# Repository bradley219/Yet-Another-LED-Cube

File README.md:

Yet-Another-LED-Cube
====================

About
-----
An attempt to reinvent..the cube? 

Sorry, this file hasn't had much effort put into it yet :/ A [video](https://fastl.io/eX6) to hold you over for now.

Schematic available in PDF and Eagle formats in the \`schematic' directory

Hardware
--------

### LED Matrix Topography

Since I only had enough hardware to create a 4x4x4 cube, I wanted the display to be as robust as
possible. I opted to use the [TLC5940](http://www.ti.com/product/tlc5940) 16-channel constant-current LED driver from Texas
Instruments, which provides 16 independent 12-bit PWM channels, each of which can sink &gt;100mA 
of current. My goal was to be able to use a single 16-channel driver to drive all 192 channels by
using a multiplexing scheme. To acheive this, I grouped the LEDs into individual "pages" of 4 LEDs.
The LEDs within a "page" share a common anode; cathodes are shared among LEDs in corresponding
positions within other pages.

### Drive Theory and Timing

The design of the cube allows for only a single "page" of LEDs to be driven at any given moment. The
16 pages which make up the cube are driven in sequence at about 100Hz (full-cycle period). 

### High-Side Switching
### Low-Side Switching/Current Sink

Software
--------

### Driver
### Driver Interface
### Color Calculations
### Animations

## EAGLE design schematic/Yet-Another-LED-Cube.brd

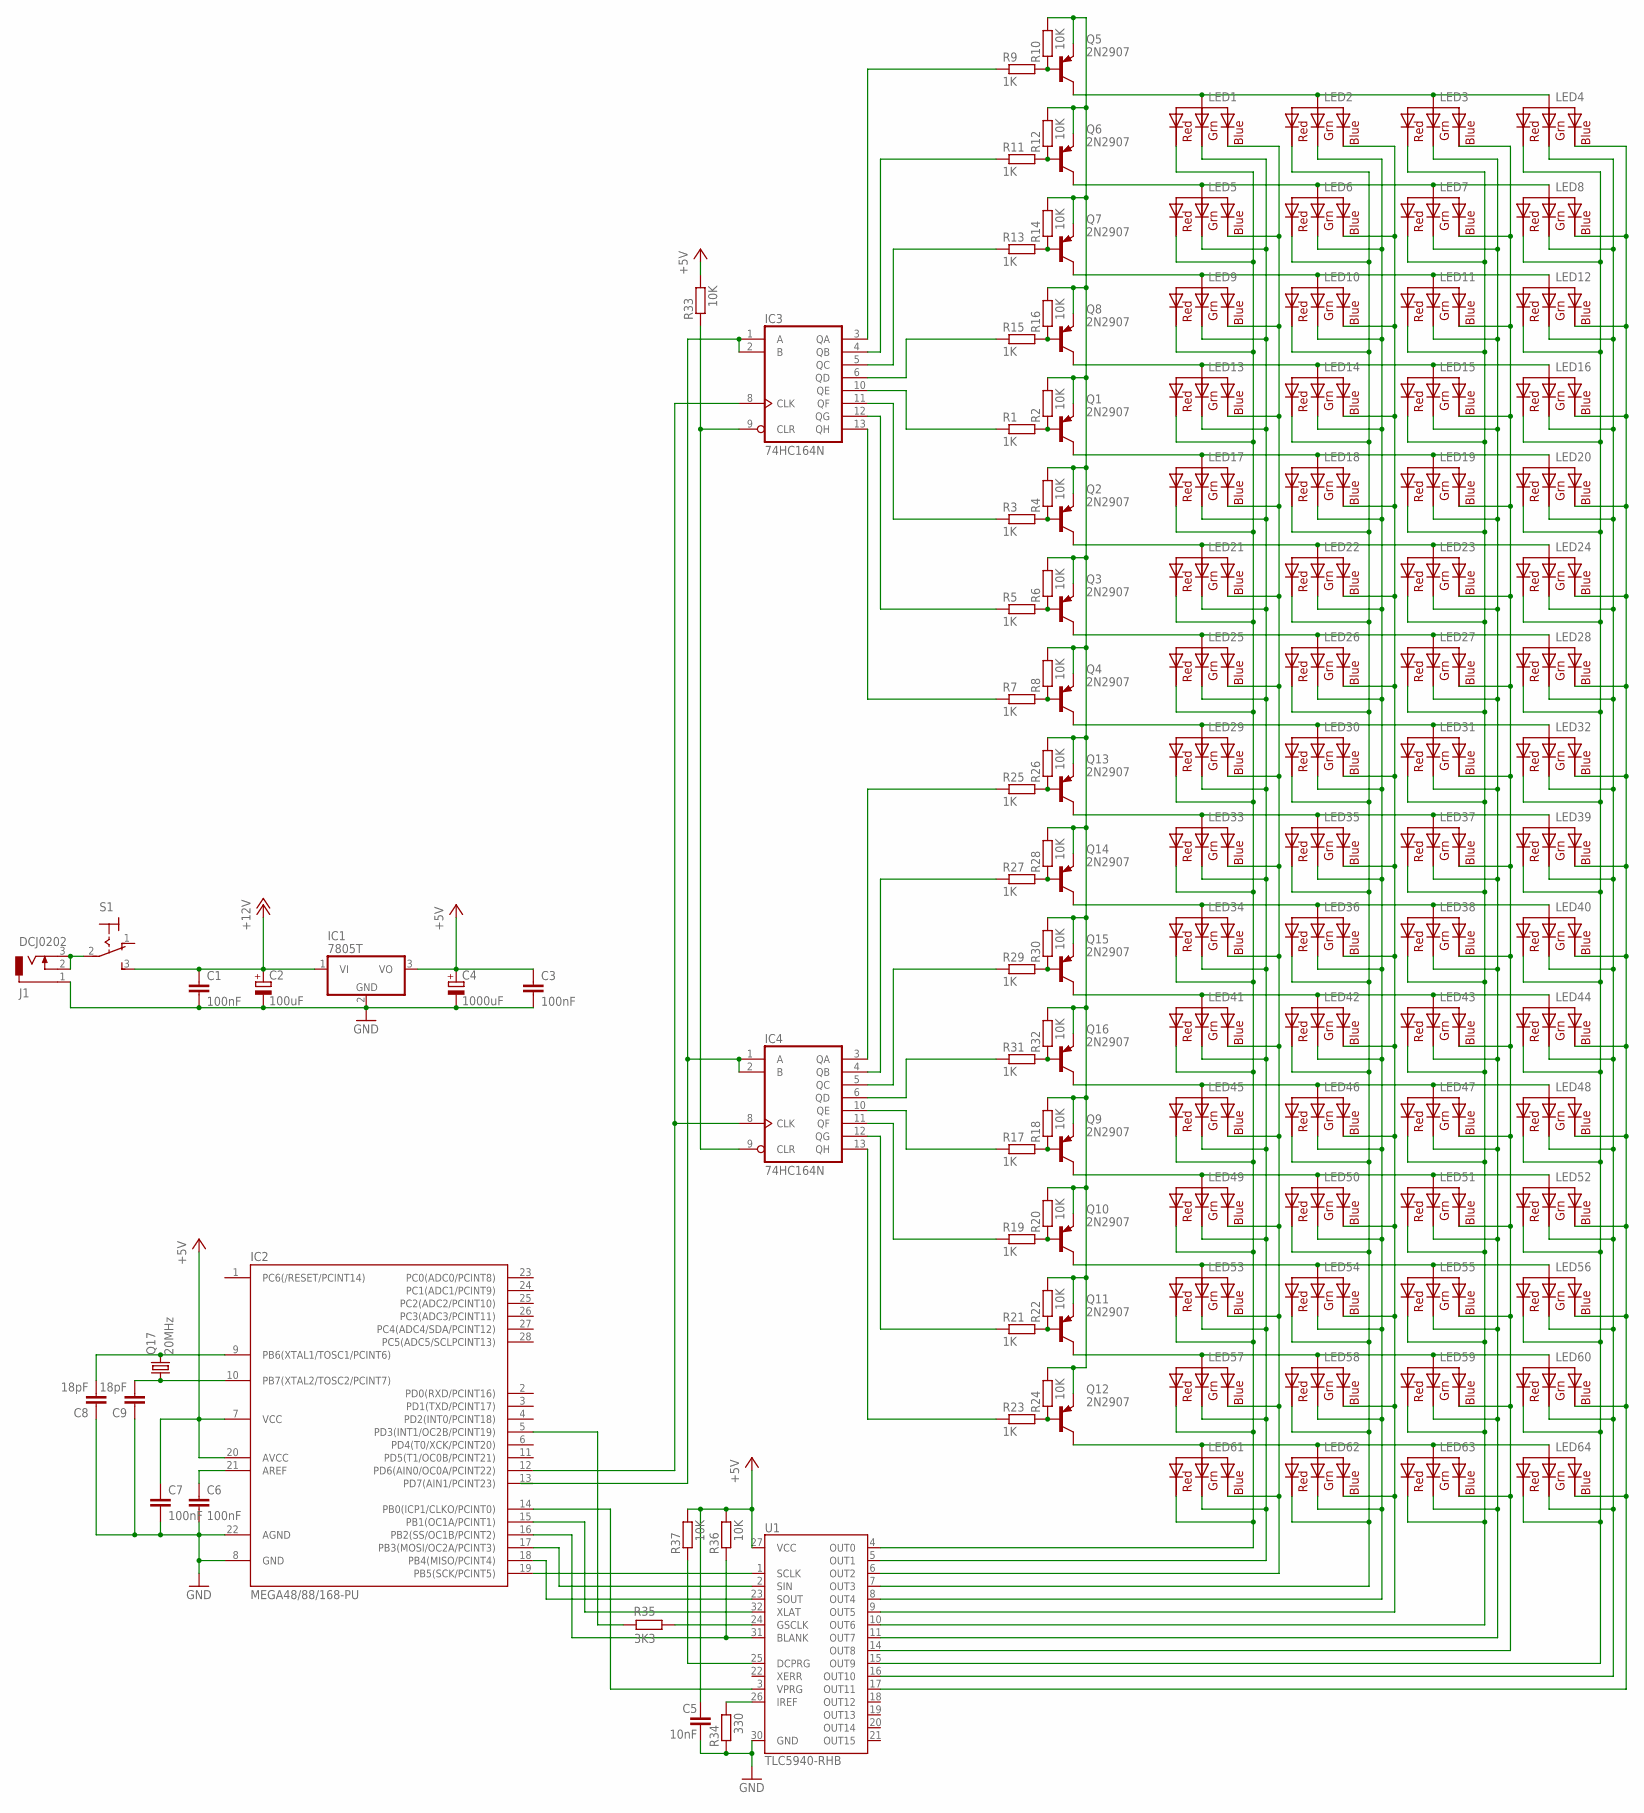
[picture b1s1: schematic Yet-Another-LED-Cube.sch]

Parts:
C1, C3, C6, C7: 100nF; C025-024X044
C2: 100uF; E2,5-7
C4: 1000uF; E3,5-10
C5: 10nF; C025-024X044
C8, C9: 18pF; C025-024X044
IC1: 7805T; TO220H
IC2: MEGA48/88/168-PU; DIL28-3
IC3, IC4: 74HC164N; DIL14
J1: DCJ0202
LED1, LED2, LED3, LED4, LED5, LED6, LED7, LED8, LED9, LED10, LED11, LED12, LED13, LED14, LED15, LED16, LED17, LED18, LED19, LED20, LED21, LED22, LED23, LED24, LED25, LED26, LED27, LED28, LED29, LED30, LED31, LED32, LED33, LED34, LED35, LED36, LED37, LED38, LED39, LED40, LED41, LED42, LED43, LED44, LED45, LED46, LED47, LED48, LED49, LED50, LED51, LED52, LED53, LED54, LED55, LED56, LED57, LED58, LED59, LED60, LED61, LED62, LED63, LED64: RGBLED_CAA; LED5MMRGB2
Q1, Q2, Q3, Q4, Q5, Q6, Q7, Q8, Q9, Q10, Q11, Q12, Q13, Q14, Q15, Q16: 2N2907; TO18
Q17: 20MHz; HC49/S
R1, R3, R5, R7, R9, R11, R13, R15, R17, R19, R21, R23, R25, R27, R29, R31: 1K; 0204V
R2, R4, R6, R8, R10, R12, R14, R16, R18, R20, R22, R24, R26, R28, R30, R32, R33, R36, R37: 10K; 0204V
R34: 330; 0204V
R35: 3K3; 0204V
S1: 320-916
U1: TLC5940-RHB; QFN-32

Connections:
+5V: C3.1, C4.+, C5.1, C7.1, IC1.3 (VO), IC2.7 (VCC), IC2.20 (AVCC), R33.2, R36.2, R37.2, U1.27 (VCC)
+12V: C1.1, C2.+, IC1.1 (VI), S1.3 (S)
GND: C1.2, C2.-, C3.2, C4.-, C5.2, C6.2, C7.2, C8.1, C9.1, IC1.2 (GND), IC2.8 (GND), IC2.22 (AGND), IC3.7 (GND), IC4.7 (GND), J1.1, R34.1, U1.30 (GND)
unnamed: J1.2, J1.3, S1.2
unnamed: Q1.2 (B), R1.2, R2.1
unnamed: Q2.2 (B), R3.2, R4.1
unnamed: Q3.2 (B), R5.2, R6.1
unnamed: Q4.2 (B), R7.2, R8.1
unnamed: Q5.2 (B), R9.2, R10.1
unnamed: Q6.2 (B), R11.2, R12.1
unnamed: Q7.2 (B), R13.2, R14.1
unnamed: Q8.2 (B), R15.2, R16.1
unnamed: LED1.P$1 (RED), LED5.P$1 (RED), LED9.P$1 (RED), LED13.P$1 (RED), LED17.P$1 (RED), LED21.P$1 (RED), LED25.P$1 (RED), LED29.P$1 (RED), LED33.P$1 (RED), LED34.P$1 (RED), LED41.P$1 (RED), LED45.P$1 (RED), LED49.P$1 (RED), LED53.P$1 (RED), LED57.P$1 (RED), LED61.P$1 (RED), U1.4 (OUT0)
unnamed: IC3.12 (QG), R5.1
unnamed: IC3.11 (QF), R3.1
unnamed: IC3.10 (QE), R1.1
unnamed: IC3.3 (QA), R9.1
unnamed: IC3.4 (QB), R11.1
unnamed: IC3.5 (QC), R13.1
unnamed: IC3.6 (QD), R15.1
unnamed: LED1.P$3 (GREEN), LED5.P$3 (GREEN), LED9.P$3 (GREEN), LED13.P$3 (GREEN), LED17.P$3 (GREEN), LED21.P$3 (GREEN), LED25.P$3 (GREEN), LED29.P$3 (GREEN), LED33.P$3 (GREEN), LED34.P$3 (GREEN), LED41.P$3 (GREEN), LED45.P$3 (GREEN), LED49.P$3 (GREEN), LED53.P$3 (GREEN), LED57.P$3 (GREEN), LED61.P$3 (GREEN), U1.5 (OUT1)
unnamed: Q9.2 (B), R17.2, R18.1
unnamed: Q10.2 (B), R19.2, R20.1
unnamed: Q11.2 (B), R21.2, R22.1
unnamed: Q12.2 (B), R23.2, R24.1
unnamed: Q13.2 (B), R25.2, R26.1
unnamed: Q14.2 (B), R27.2, R28.1
unnamed: Q15.2 (B), R29.2, R30.1
unnamed: Q16.2 (B), R31.2, R32.1
unnamed: IC4.12 (QG), R21.1
unnamed: IC4.11 (QF), R19.1
unnamed: IC4.10 (QE), R17.1
unnamed: IC4.3 (QA), R25.1
unnamed: IC4.4 (QB), R27.1
unnamed: IC4.5 (QC), R29.1
unnamed: IC4.6 (QD), R31.1
unnamed: IC2.19 (PB5(SCK/PCINT5)), U1.1 (SCLK)
unnamed: LED1.P$2 (VCC), LED2.P$2 (VCC), LED3.P$2 (VCC), LED4.P$2 (VCC), Q5.3 (C)
unnamed: IC2.12 (PD6(AIN0/OC0A/PCINT22)), IC3.8 (CLK), IC4.8 (CLK)
unnamed: IC3.1 (A), IC3.2 (B), IC4.1 (A), IC4.2 (B)
unnamed: LED1.P$4 (BLUE), LED5.P$4 (BLUE), LED9.P$4 (BLUE), LED13.P$4 (BLUE), LED17.P$4 (BLUE), LED21.P$4 (BLUE), LED25.P$4 (BLUE), LED29.P$4 (BLUE), LED33.P$4 (BLUE), LED34.P$4 (BLUE), LED41.P$4 (BLUE), LED45.P$4 (BLUE), LED49.P$4 (BLUE), LED53.P$4 (BLUE), LED57.P$4 (BLUE), LED61.P$4 (BLUE), U1.6 (OUT2)
unnamed: IC2.17 (PB3(MOSI/OC2A/PCINT3)), U1.2 (SIN)
unnamed: IC3.9 (CLR), IC4.9 (CLR), R33.1
unnamed: LED5.P$2 (VCC), LED6.P$2 (VCC), LED7.P$2 (VCC), LED8.P$2 (VCC), Q6.3 (C)
unnamed: LED2.P$1 (RED), LED6.P$1 (RED), LED10.P$1 (RED), LED14.P$1 (RED), LED18.P$1 (RED), LED22.P$1 (RED), LED26.P$1 (RED), LED30.P$1 (RED), LED35.P$1 (RED), LED36.P$1 (RED), LED42.P$1 (RED), LED46.P$1 (RED), LED50.P$1 (RED), LED54.P$1 (RED), LED58.P$1 (RED), LED62.P$1 (RED), U1.7 (OUT3)
unnamed: LED2.P$3 (GREEN), LED6.P$3 (GREEN), LED10.P$3 (GREEN), LED14.P$3 (GREEN), LED18.P$3 (GREEN), LED22.P$3 (GREEN), LED26.P$3 (GREEN), LED30.P$3 (GREEN), LED35.P$3 (GREEN), LED36.P$3 (GREEN), LED42.P$3 (GREEN), LED46.P$3 (GREEN), LED50.P$3 (GREEN), LED54.P$3 (GREEN), LED58.P$3 (GREEN), LED62.P$3 (GREEN), U1.8 (OUT4)
unnamed: LED2.P$4 (BLUE), LED6.P$4 (BLUE), LED10.P$4 (BLUE), LED14.P$4 (BLUE), LED18.P$4 (BLUE), LED22.P$4 (BLUE), LED26.P$4 (BLUE), LED30.P$4 (BLUE), LED35.P$4 (BLUE), LED36.P$4 (BLUE), LED42.P$4 (BLUE), LED46.P$4 (BLUE), LED50.P$4 (BLUE), LED54.P$4 (BLUE), LED58.P$4 (BLUE), LED62.P$4 (BLUE), U1.9 (OUT5)
unnamed: IC3.13 (QH), R7.1
unnamed: LED3.P$1 (RED), LED7.P$1 (RED), LED11.P$1 (RED), LED15.P$1 (RED), LED19.P$1 (RED), LED23.P$1 (RED), LED27.P$1 (RED), LED31.P$1 (RED), LED37.P$1 (RED), LED38.P$1 (RED), LED43.P$1 (RED), LED47.P$1 (RED), LED51.P$1 (RED), LED55.P$1 (RED), LED59.P$1 (RED), LED63.P$1 (RED), U1.10 (OUT6)
unnamed: LED3.P$3 (GREEN), LED7.P$3 (GREEN), LED11.P$3 (GREEN), LED15.P$3 (GREEN), LED19.P$3 (GREEN), LED23.P$3 (GREEN), LED27.P$3 (GREEN), LED31.P$3 (GREEN), LED37.P$3 (GREEN), LED38.P$3 (GREEN), LED43.P$3 (GREEN), LED47.P$3 (GREEN), LED51.P$3 (GREEN), LED55.P$3 (GREEN), LED59.P$3 (GREEN), LED63.P$3 (GREEN), U1.11 (OUT7)
unnamed: LED3.P$4 (BLUE), LED7.P$4 (BLUE), LED11.P$4 (BLUE), LED15.P$4 (BLUE), LED19.P$4 (BLUE), LED23.P$4 (BLUE), LED27.P$4 (BLUE), LED31.P$4 (BLUE), LED37.P$4 (BLUE), LED38.P$4 (BLUE), LED43.P$4 (BLUE), LED47.P$4 (BLUE), LED51.P$4 (BLUE), LED55.P$4 (BLUE), LED59.P$4 (BLUE), LED63.P$4 (BLUE), U1.14 (OUT8)
unnamed: IC2.18 (PB4(MISO/PCINT4)), U1.23 (SOUT)
unnamed: LED4.P$1 (RED), LED8.P$1 (RED), LED12.P$1 (RED), LED16.P$1 (RED), LED20.P$1 (RED), LED24.P$1 (RED), LED28.P$1 (RED), LED32.P$1 (RED), LED39.P$1 (RED), LED40.P$1 (RED), LED44.P$1 (RED), LED48.P$1 (RED), LED52.P$1 (RED), LED56.P$1 (RED), LED60.P$1 (RED), LED64.P$1 (RED), U1.15 (OUT9)
unnamed: LED4.P$3 (GREEN), LED8.P$3 (GREEN), LED12.P$3 (GREEN), LED16.P$3 (GREEN), LED20.P$3 (GREEN), LED24.P$3 (GREEN), LED28.P$3 (GREEN), LED32.P$3 (GREEN), LED39.P$3 (GREEN), LED40.P$3 (GREEN), LED44.P$3 (GREEN), LED48.P$3 (GREEN), LED52.P$3 (GREEN), LED56.P$3 (GREEN), LED60.P$3 (GREEN), LED64.P$3 (GREEN), U1.16 (OUT10)
unnamed: LED4.P$4 (BLUE), LED8.P$4 (BLUE), LED12.P$4 (BLUE), LED16.P$4 (BLUE), LED20.P$4 (BLUE), LED24.P$4 (BLUE), LED28.P$4 (BLUE), LED32.P$4 (BLUE), LED39.P$4 (BLUE), LED40.P$4 (BLUE), LED44.P$4 (BLUE), LED48.P$4 (BLUE), LED52.P$4 (BLUE), LED56.P$4 (BLUE), LED60.P$4 (BLUE), LED64.P$4 (BLUE), U1.17 (OUT11)
unnamed: Q1.1 (E), Q2.1 (E), Q3.1 (E), Q4.1 (E), Q5.1 (E), Q6.1 (E), Q7.1 (E), Q8.1 (E), Q9.1 (E), Q10.1 (E), Q11.1 (E), Q12.1 (E), Q13.1 (E), Q14.1 (E), Q15.1 (E), Q16.1 (E), R2.2, R4.2, R6.2, R8.2, R10.2, R12.2, R14.2, R16.2, R18.2, R20.2, R22.2, R24.2, R26.2, R28.2, R30.2, R32.2
unnamed: IC2.15 (PB1(OC1A/PCINT1)), U1.32 (XLAT)
unnamed: IC2.5 (PD3(INT1/OC2B/PCINT19)), R35.2
unnamed: IC2.16 (PB2(SS/OC1B/PCINT2)), R36.1, U1.31 (BLANK)
unnamed: IC2.14 (PB0(ICP1/CLKO/PCINT0)), U1.3 (VPRG)
unnamed: R34.2, U1.26 (IREF)
unnamed: R35.1, U1.24 (GSCLK)
unnamed: R37.1, U1.25 (DCPRG)
unnamed: LED33.P$2 (VCC), LED35.P$2 (VCC), LED37.P$2 (VCC), LED39.P$2 (VCC), Q13.3 (C)
unnamed: LED34.P$2 (VCC), LED36.P$2 (VCC), LED38.P$2 (VCC), LED40.P$2 (VCC), Q14.3 (C)
unnamed: LED61.P$2 (VCC), LED62.P$2 (VCC), LED63.P$2 (VCC), LED64.P$2 (VCC), Q12.3 (C)
unnamed: LED57.P$2 (VCC), LED58.P$2 (VCC), LED59.P$2 (VCC), LED60.P$2 (VCC), Q11.3 (C)
unnamed: LED53.P$2 (VCC), LED54.P$2 (VCC), LED55.P$2 (VCC), LED56.P$2 (VCC), Q10.3 (C)
unnamed: LED49.P$2 (VCC), LED50.P$2 (VCC), LED51.P$2 (VCC), LED52.P$2 (VCC), Q9.3 (C)
unnamed: LED45.P$2 (VCC), LED46.P$2 (VCC), LED47.P$2 (VCC), LED48.P$2 (VCC), Q16.3 (C)
unnamed: LED41.P$2 (VCC), LED42.P$2 (VCC), LED43.P$2 (VCC), LED44.P$2 (VCC), Q15.3 (C)
unnamed: IC4.13 (QH), R23.1
unnamed: C6.1, IC2.21 (AREF)
unnamed: C8.2, IC2.9 (PB6(XTAL1/TOSC1/PCINT6)), Q17.2
unnamed: C9.2, IC2.10 (PB7(XTAL2/TOSC2/PCINT7)), Q17.1
unnamed: LED29.P$2 (VCC), LED30.P$2 (VCC), LED31.P$2 (VCC), LED32.P$2 (VCC), Q4.3 (C)
unnamed: LED25.P$2 (VCC), LED26.P$2 (VCC), LED27.P$2 (VCC), LED28.P$2 (VCC), Q3.3 (C)
unnamed: LED21.P$2 (VCC), LED22.P$2 (VCC), LED23.P$2 (VCC), LED24.P$2 (VCC), Q2.3 (C)
unnamed: LED17.P$2 (VCC), LED18.P$2 (VCC), LED19.P$2 (VCC), LED20.P$2 (VCC), Q1.3 (C)
unnamed: LED13.P$2 (VCC), LED14.P$2 (VCC), LED15.P$2 (VCC), LED16.P$2 (VCC), Q8.3 (C)
unnamed: LED9.P$2 (VCC), LED10.P$2 (VCC), LED11.P$2 (VCC), LED12.P$2 (VCC), Q7.3 (C)
VCC: IC3.14 (VCC), IC4.14 (VCC)

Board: 2 copper layers, 134 parts (0 on the bottom side), 82 nets, no tracks yet.

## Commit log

2012-07-02 Interrupt-based latching
2012-07-02 adj params to fix choppiness
2012-07-03 tried to equalize color intensities
2012-07-05 makefile
2012-07-05 added 4 rows; color adjustments
2012-07-05 started cube sliders
2012-07-06 started separating into separate files
2012-07-06 cube sliders
2012-07-06 translated some driver functions into assembly
2012-07-07 Refactored the LED driver core
2012-07-08 Changed random seed method to eeprom-based
2012-07-08 More asm driver conversions
2012-07-08 ISR routine converted to asm
2012-07-08 asm tuning
2012-07-08 pointer issue in cube function
2012-07-08 Timing data from logic analyzer
2012-07-08 Deleted unnecessary XLAT interrupt pulse
2012-07-08 Added fader sequence
2012-07-09 added snake module
2012-07-09 added missing files
2012-07-09 snake objects without C++!
2012-07-09 fixed PWM timing err found w/oscilloscope
2012-07-11 Interrupt-based SPI data latching
2012-07-11 Worked out all ISR kinks with new driver
2012-07-11 Perfected timing by counting clk cycles
2012-07-11 Fixed gs data pointer initialization
2012-07-11 Perfect for now
2012-07-12 Pre-analog commit
2012-07-12 Eeek!
2012-07-12 Ahh fixed
2012-07-13 Added beat detection test
2012-07-18 Audio looks nice
2012-07-21 audio snake
2012-07-21 audio snakes delay fixed
2012-07-22 snakes flash on audio beats
2012-07-22 Optimized SPI ISR routine in assembly
2012-07-22 gitignore updated
2012-07-22 readme file updated
2012-07-30 minor
2012-08-06 Everything works checkpoint
2012-08-06 working 2
2012-08-07 MOV071.mp4
    https://www.dropbox.com/s/au3ys8abuv36xhp/MOV071.mp4
2012-08-14 added board
2012-08-14 added a bunch of parts
2012-08-14 removed shadow files
2012-08-15 Changed shift register port/pin defs
2012-08-15 Add RGB LED parts; connect IC's
2012-08-15 Add PDF version of schematic
2012-08-18 bunch of random stuff
2012-08-18 start panels animation venture
2012-08-18 adjust snake brightness
2012-08-18 Organize files
2012-08-18 remove gitignore file
2012-08-18 add image
2012-08-18 add JPEG preview of schematic
2012-08-18 add schematic to readme file
2012-08-18 update schematic
2012-08-18 add LED page unit diagram
2012-08-18 shrink led page image
2012-08-18 remove typo
2012-08-19 start line-rendering utils
2012-08-19 triangles
2012-09-05 readme: drive theory & matrix topo
2012-09-05 add tlc5940 link
2012-09-05 readme
2019-07-26 Fix video link in README.md
    Issue #1
2019-07-26 fix markdown syntax
